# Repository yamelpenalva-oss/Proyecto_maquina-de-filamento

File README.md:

"# Proyecto_maquina-de-filamento"

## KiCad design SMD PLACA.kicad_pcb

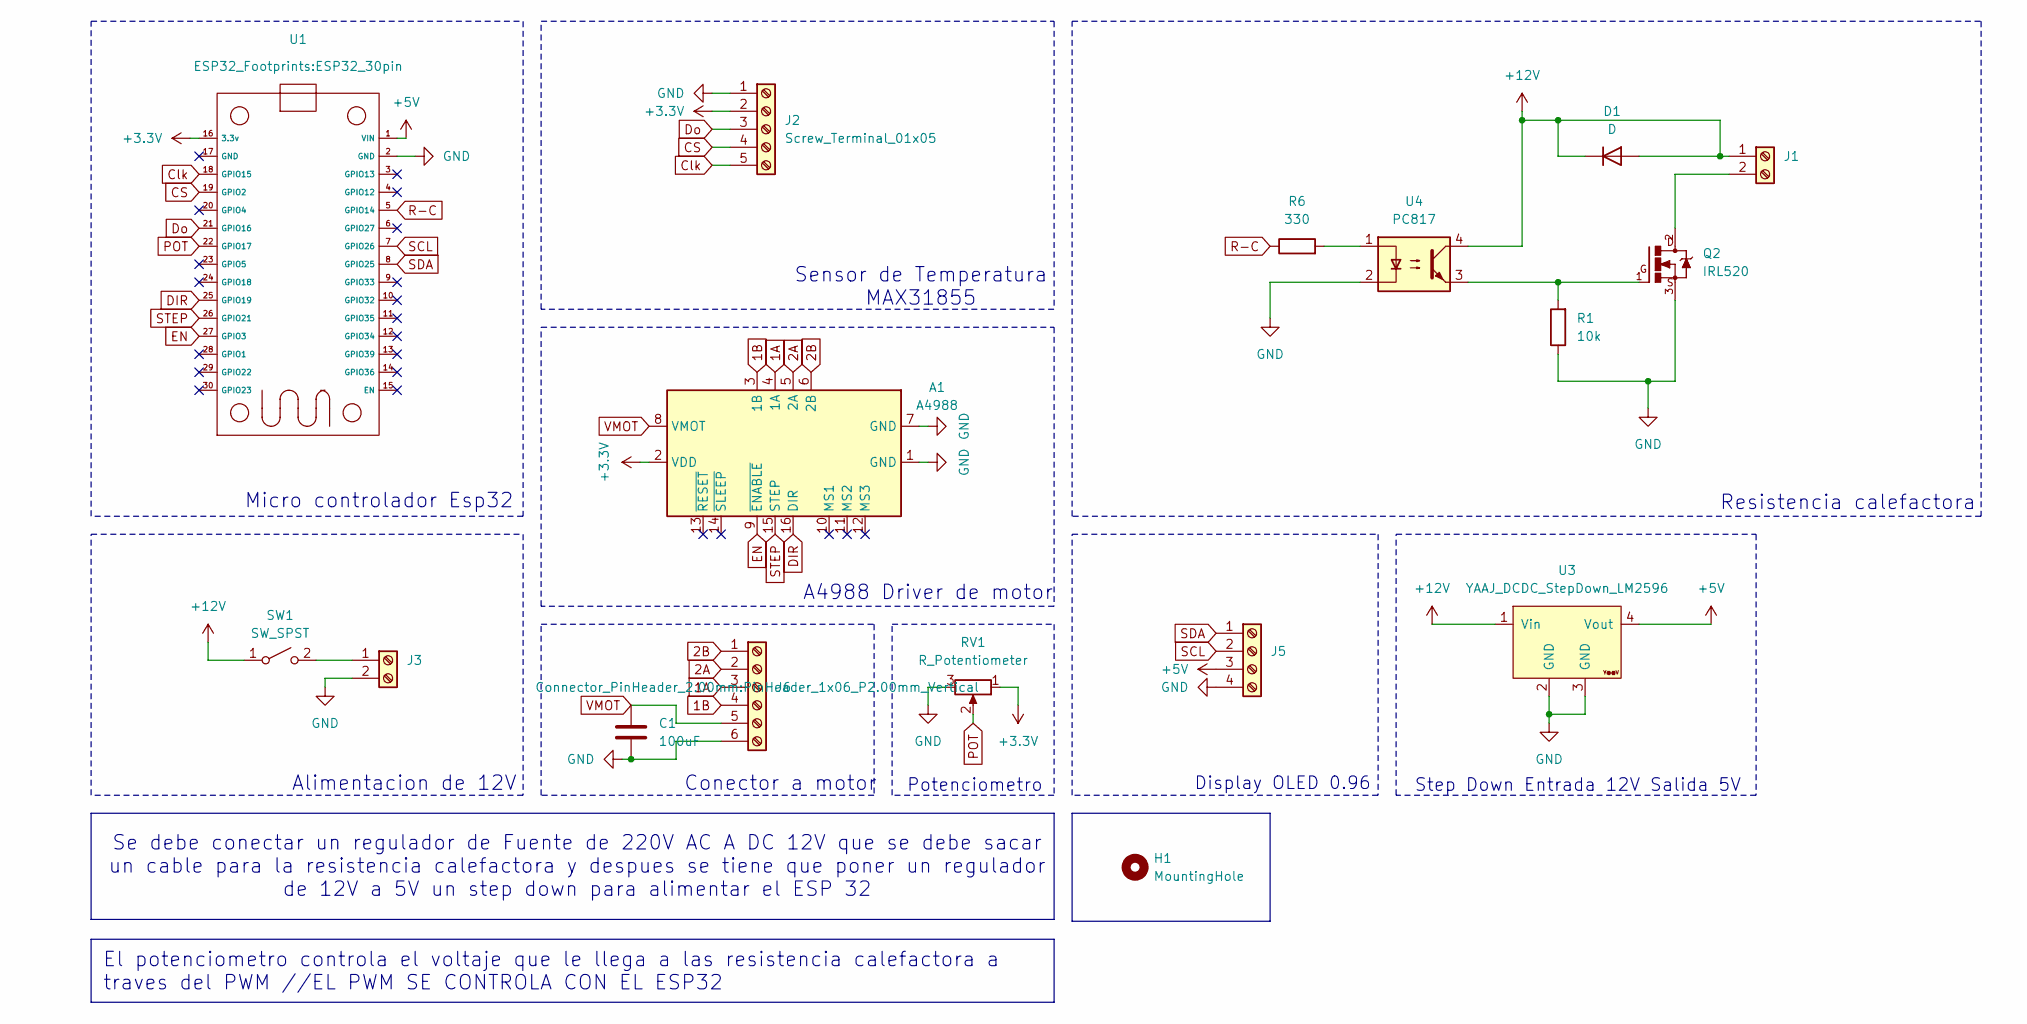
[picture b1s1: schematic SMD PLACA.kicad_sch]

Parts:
A1: A4988; MODULE_A4988_STEPPER_MOTOR_DRIVER_CARRIER
C1: 100uF; C_Disc_D3.0mm_W1.6mm_P2.50mm
D1: D; D_0805_2012Metric_Pad1.15x1.40mm_HandSolder
H1: MountingHole
J1, J3: Screw_Terminal_01x02; TerminalBlock_Phoenix_MKDS-1,5-2-5.08_1x02_P5.08mm_Horizont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
J2: Screw_Terminal_01x05; PinHeader_1x05_P2.00mm_Vertical
J5: Screw_Terminal_01x04; PinHeader_1x04_P2.00mm_Vertical
J6: Screw_Terminal_01x06; PinHeader_1x06_P2.00mm_Vertical
Q2: IRL520; TO-220-3_Vertical
R1: 10k; R_0805_2012Metric
R6: 330; R_0805_2012Metric
RV1: R_Potentiometer; SW_ATE1D-2M3-10-Z
SW1: SW_SPST; SW_ATE1D-2M3-10-Z
U1: ESP32_30pin
U3: YAAJ_DCDC_StepDown_LM2596
U4: PC817; SOIC254P960X420-4N

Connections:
1A: A1.4 (1A), J6.3
1B: A1.3 (1B), J6.4
2A: A1.5 (2A), J6.2
2B: A1.6 (2B), J6.1
+3.3V: A1.2 (VDD), J2.2, RV1.1, U1.16 (3.3v)
+5V: J5.3, U1.1 (VIN), U3.4 (Vout)
+12V: D1.1 (K), D1.2 (A), J1.1, SW1.1 (A), U3.1 (Vin), U4.4
CS: J2.4, U1.19 (GPIO2)
Clk: J2.5, U1.18 (GPIO15)
DIR: A1.16 (DIR), U1.25 (GPIO19)
Do: J2.3, U1.21 (GPIO16)
EN: A1.9 (~ENABLE), U1.27 (GPIO3)
GND: A1.1 (GND), A1.7 (GND), C1.2, J2.1, J3.2, J5.4, J6.6, Q2.3, R1.1, RV1.3, U1.2 (GND), U3.2 (GND), U3.3 (GND), U4.2
unnamed: J1.2, Q2.2
unnamed: J3.1, SW1.2 (B)
unnamed: Q2.1, R1.2, U4.3
unnamed: R6.2, U4.1
POT: RV1.2, U1.22 (GPIO17)
R-C: R6.1, U1.5 (GPIO14)
SCL: J5.2, U1.7 (GPIO26)
SDA: J5.1, U1.8 (GPIO25)
STEP: A1.15 (STEP), U1.26 (GPIO21)
VMOT: A1.8 (VMOT), C1.1, J6.5

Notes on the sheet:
El potenciometro controla el voltaje que le llega a las resistencia calefactora a traves del PWM //EL PWM SE CONTROLA CON EL ESP32
Alimentacion de 12V
Se debe conectar un regulador de Fuente de 220V AC A DC 12V que se debe sacar un cable para la resistencia calefactora y despues se tiene que poner un regulador de 12V a 5V un step down para alimentar el ESP 32
Resistencia calefactora
Step Down Entrada 12V Salida 5V
Conector a motor
Display OLED 0.96
A4988 Driver de motor
Sensor de Temperatura MAX31855
Potenciometro
Micro controlador Esp32

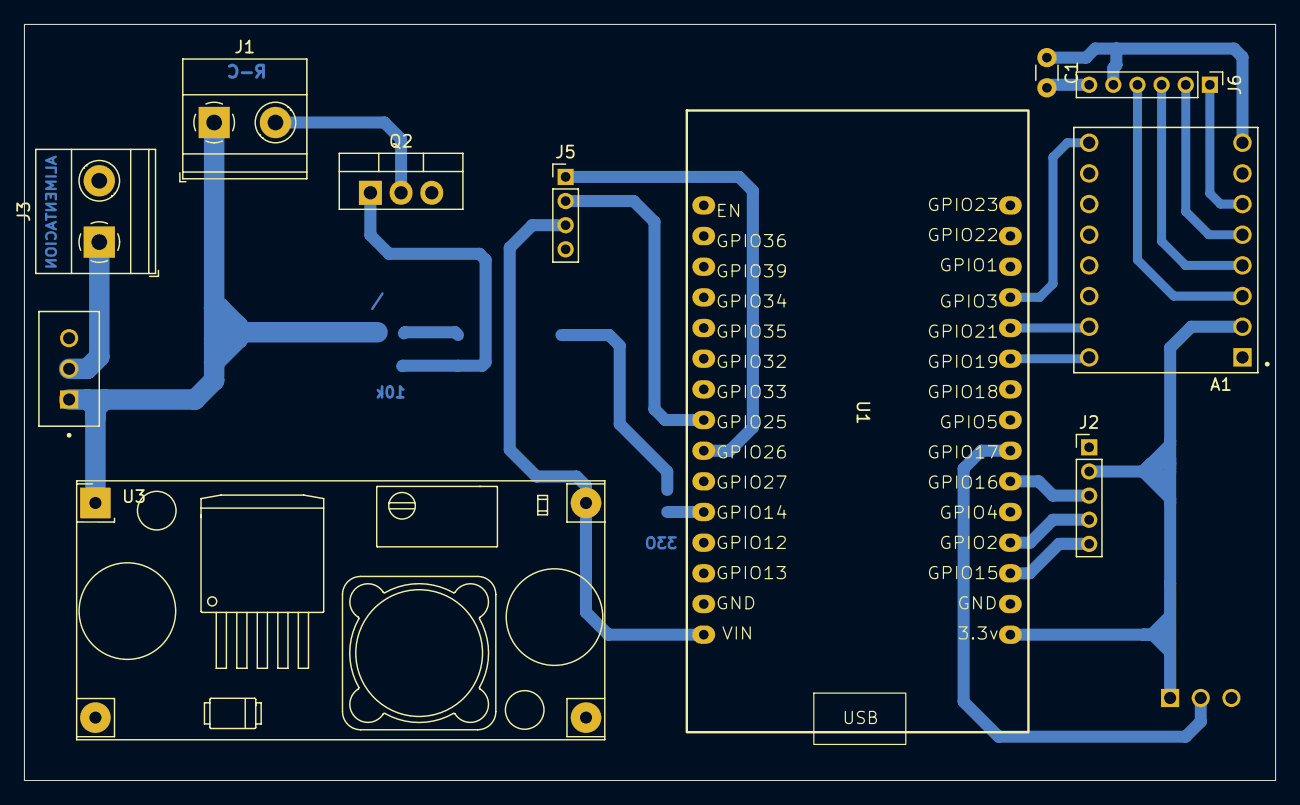
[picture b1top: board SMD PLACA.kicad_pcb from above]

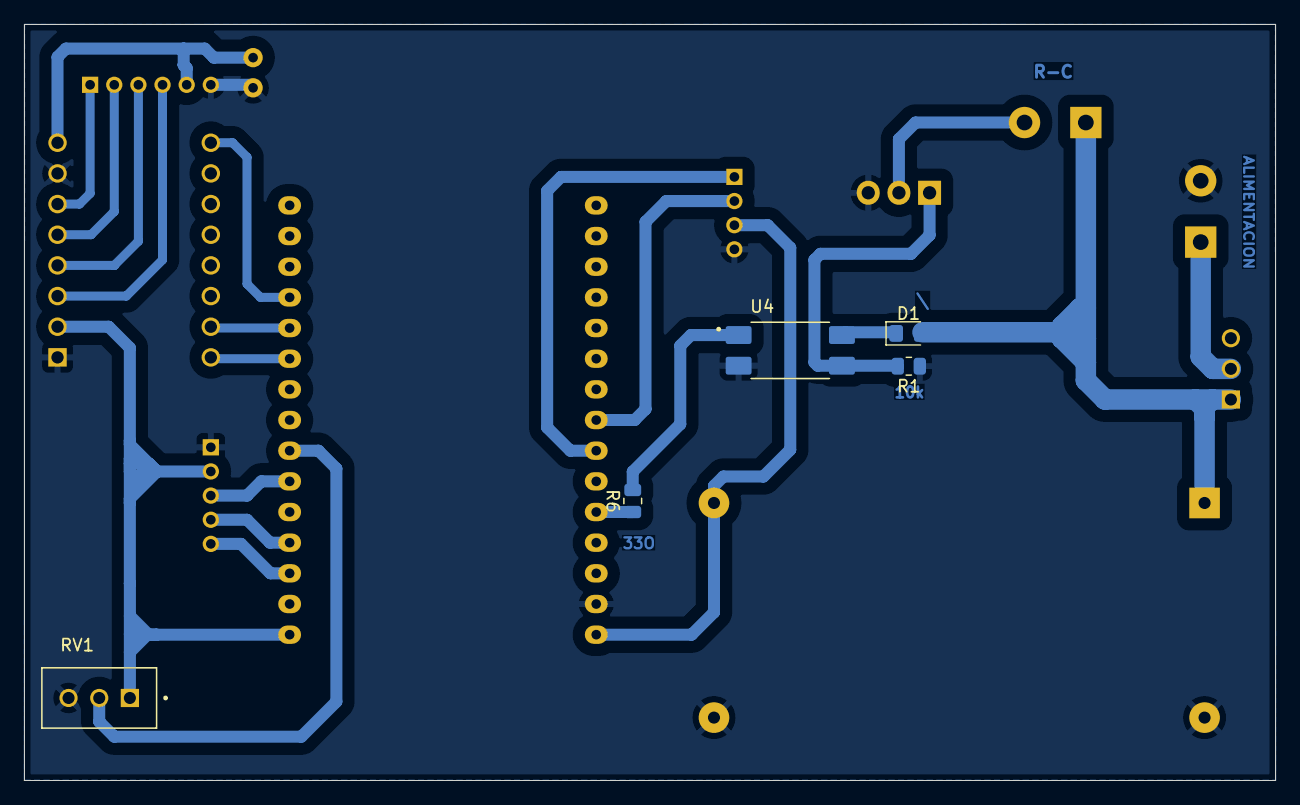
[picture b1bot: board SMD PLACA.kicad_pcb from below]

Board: 2 copper layers, 103.6 x 62.6 mm, 17 parts (5 on the bottom side), 23 nets.
